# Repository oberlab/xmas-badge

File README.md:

<p align="center">
<h1 align="center">XMas LED Badge (educational PCB)</h1>
<h3 align="center">Christmas decoration for maker</h3>
</p>

<br>
<br>

## Instructions
We used this PCB as part of an educational workshop about electronics. The instructions and exercises for the students are in the folder edu_resources. Unfortunately they are just available in German for now. Feel free to translate them and file a pull-request.

## Parts
You can find a list of the required parts in the 1-click-BOM.csv file. It lists all the respective products at part resellers. However, for some standard parts such as the 5 mm LEDs and the switches you might want to consider buying them in bulk from another supplier because it'll be much cheaper. Here are some links:
- [slider switch](https://de.aliexpress.com/item/4000091720006.html)
- [CR1225 battery clip](https://de.aliexpress.com/item/4000273116875.html)

## About & Attribution

### PCB Design
The PCB was designed using [KiCAD](https://www.kicad.org/) in combination with the [svg2shenzhen plugin](https://github.com/badgeek/svg2shenzhen) for [Inkscape](https://inkscape.org/). A big thank you to [badgeek](https://github.com/badgeek) for developing and maintaining this awesome piece of software which got me into PCB designe in the first place

### PCB manufacturing
PCBs were manufactured by [PCBWay](https://www.pcbway.com/) (sponsored). Order process was very simple, customer service friendly and the quality of the PCBs is great! Thanks to PCBWay for sponsoring this project and thus made our christmas workshop with local students possible.
<p align="center">

<p align="center">

## License
The PCB is licenced under the CERN-OHL-W license and everything else (README, instructions and templates) under CC-BY-SA 4.0

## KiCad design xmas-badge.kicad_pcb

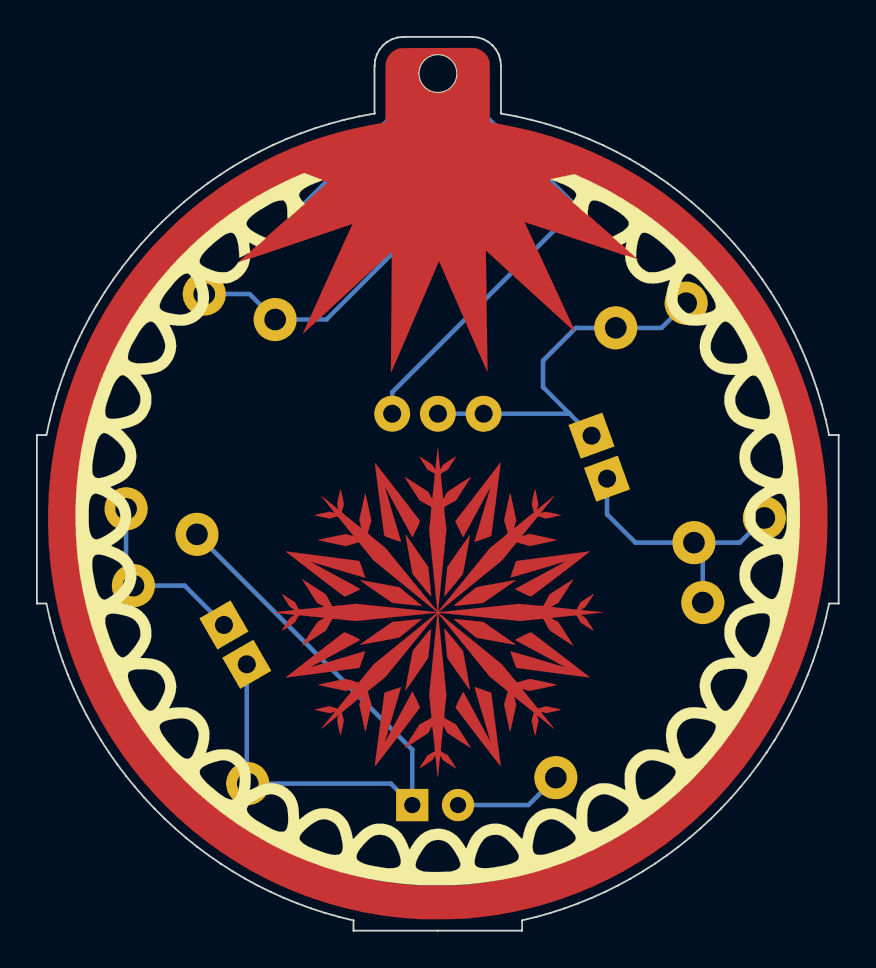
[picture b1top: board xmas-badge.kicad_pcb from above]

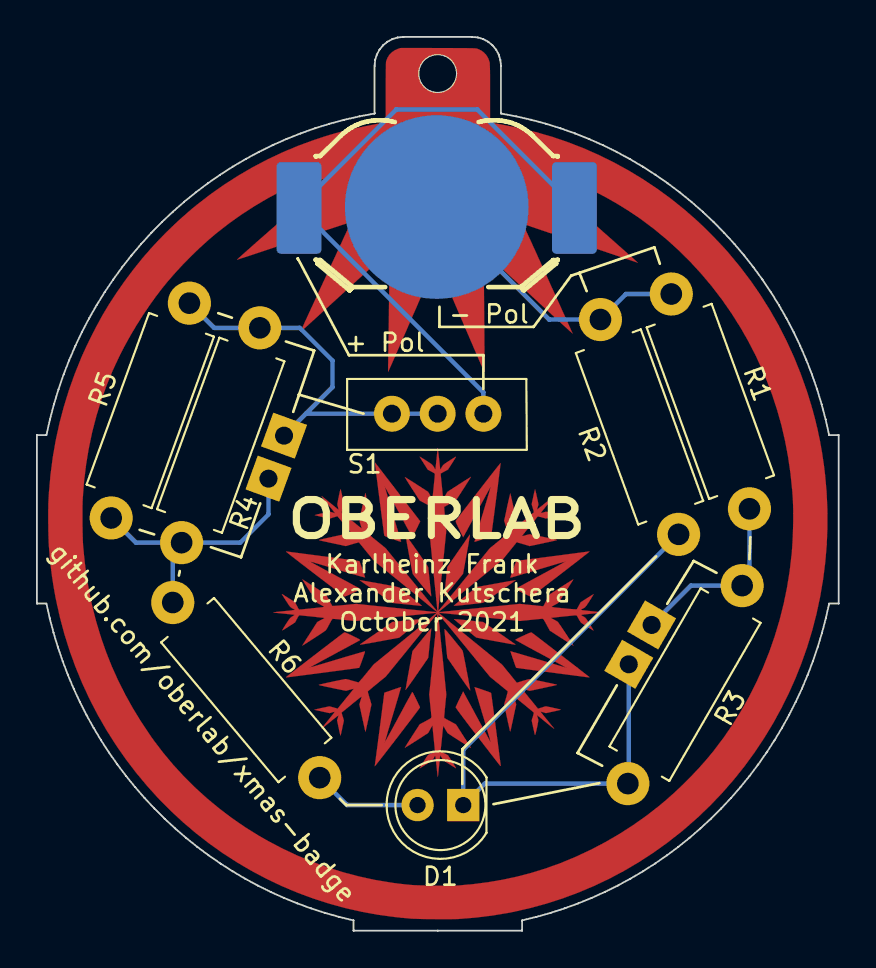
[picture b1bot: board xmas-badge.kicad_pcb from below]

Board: 2 copper layers, 44.5 x 49.7 mm, 14 parts (10 on the bottom side), 7 nets.

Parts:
 : MountingHole_2.1mm
 #2,  #3,  #4,  #5: LP
D1: LED; LED_D5.0mm
R1, R2, R3, R4, R5, R6: R; R_Axial_DIN0411_L9.9mm_D3.6mm_P12.70mm_Horizontal
S1: Micro_Schalter; Micro_SchalterKHF
U1: BAT_HLD_2032; BAT-HLD-012-SMT

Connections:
unnamed: #3.1, D1.1, R2.1, R3.1
unnamed: D1.2, R6.1
unnamed: #2.1, R1.1, R3.2
unnamed: R1.2, R2.2, U1.1
unnamed: #5.1, R4.1, R5.1, R6.2
unnamed: #4.1, R4.2, R5.2, S1.2, S1.3
unnamed: S1.1, U1.2, U1.3

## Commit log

2021-10-07 Uploaded files
2021-10-07 added KiCad files
2021-10-23 first small version
2021-10-23 saved
2021-10-23 increased size, component placement
2021-12-21 updated README, improved instructions
2026-05-03 Save local changes before system wipe
